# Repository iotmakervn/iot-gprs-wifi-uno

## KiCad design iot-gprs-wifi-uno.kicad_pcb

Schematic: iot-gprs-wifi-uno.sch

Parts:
C1: 10uF/50V; C_1210
C2: 10uF/50v; C_1210
C3: 1uF; C_0603
C4, C6, C15: 22pF; C_0603
C5, C10, C14, C22: 100nF; C_0603
C7, C8: 10uF/25V; C_1210
C9: 22uF; C_0603
C11: 100pF; C_0603
C12: 470uF; C_0603
C13: 10uF; C_0603
C16: 1uF/25V; C_1210
C17: 1uF/25V; C_0603
C18, C19, C20, C21: 0.1uF; C_0603
CON1: BARREL_JACK; dc_socket
D1, D3: SS24; do214aa
D2: D_Zener; SOD-80
D4: L_PWR; LED_0603
D5: LED_blue; LED_0603
L1: 22uH; Choke_SMD_Wuerth-WE-PD2-Typ-MS
P1: CAMERASOCKET; camera_socket24aaa
P2: SW2x6; SW_DIP_x6_W8.61mm_Slide_SMD_LowProfile
P3, P6: CONN_01X08; Pin_Header_Straight_1x08_Pitch2.54mm
P4: CONN_01X10; Pin_Header_Straight_1x10_Pitch2.54mm
P5: CONN_01X06; Pin_Header_Straight_1x06_Pitch2.54mm
R1, R3, R12, R16: NC; R_0603
R2, R15: 0K; R_0603
R4: 52.5K; R_0603
R5, R24, R25, R26, R27: 10K; R_0603
R6: 100R; R_0603
R7, R9, R28, R30: 470R; R_0603
R8: 10R; R_0603
R10, R11, R13: 10k; R_0603
R17: 3K/1%; R_0603
R18, R20, R21, R22, R23: 1K/1%; R_0603
R19: 470K; R_0603
R29: OR; R_0603
SMA1, SMA2: SMA; ANTEN_FP
SW1: SW_PUSH; SW_SPST_B3U-1000P
U1: usb_mini_b; USB_Micro-B
U2: MCP16311-MNY; MSOP-8_3x3mm_Pitch0.65mm
U3: CH340G; soic-16
U4: A20Module; a20module
U5: MCP6001R; SOT-23-5
U6: IRLM6402; SOT-23
U7: BD00GA5WEFJ; SOIJ-8_5.3x5.3mm_Pitch1.27mm
U8: SIM; SIM_HOLD_115A-ADA0-R02
X1: CRYSTAL_ABM3C; Crystal_SMD_3225_12MHz

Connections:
CAM_CLK: P1.13, U4.12
CAM_HREF: P1.9, U4.13
CAM_PCLK: P1.17, U4.11
CAM_PDN: P1.8, U4.41
CAM_RST: P1.6, U4.43
CAM_VSYNC: P1.7, U4.9
CAM_Y0: P1.19, U4.10
CAM_Y1: P1.21, U4.1
CAM_Y2: P1.22, U4.2
CAM_Y3: P1.20, U4.3
CAM_Y4: P1.18, U4.4
CAM_Y5: P1.16, U4.5
CAM_Y6: P1.14, U4.6
CAM_Y7: P1.12, U4.7
D+: U1.3 (D+), U3.5 (D+)
D-: U1.2 (D-), U3.6 (D-)
FLASH_EN: U4.38
FLASH_LED-: R22.2
GPIO3: U4.40
HST_RXD: P6.6, U4.37
HST_TXD: U4.36
I2C_SCL: R23.2, U4.31
I2C_SDA: R21.2, U4.30
unnamed: C3.1, U2.2 (Vcc)
unnamed: C4.1, X1.1
unnamed: C5.1, U2.7 (BOOST)
unnamed: C5.2, L1.1, U2.6 (SW)
unnamed: C10.1, U3.4 (3V)
unnamed: C22.1, R26.2
unnamed: CON1.1, D1.2 (A)
unnamed: D4.2 (A), R19.2
unnamed: D5.1 (K), R29.2
unnamed: D5.2 (A), R28.1
unnamed: P1.3, R21.1
unnamed: P1.5, R23.1
unnamed: P1.23, R20.1
unnamed: P1.24, R22.1
unnamed: R1.1, R2.2, U4.21
unnamed: R2.1, R3.2, SMA1.3
unnamed: R5.1, U4.18
unnamed: R7.1, U3.2 (TxD)
unnamed: R9.1, U3.3 (RxD)
unnamed: R10.2, R11.1, U5.3 (+)
unnamed: R12.2, R15.2, U4.39
unnamed: R4.2, R13.1, U2.1 (Vfb)
unnamed: R15.1, R16.2, SMA2.3
unnamed: R17.1, R18.1, U7.2 (FB)
unnamed: R29.1, R30.1, SW1.1
unnamed: U5.1, U6.1
SIM_CLK: U4.15, U8.3
SIM_DATA: U4.17, U8.7
SIM_RST: U4.14, U8.2
SLEEP: R5.2, U4.35
UART_RXD: P2.1, P2.2, R7.2, U4.33
UART_TXD: P2.3, P2.4, R9.2, U4.34
U_RXD: P2.12, P6.8
U_TXD: P2.10, P6.7
VCC3.3: C9.2, C11.2, C17.2, P3.5, R17.2, R19.1, R24.1, R25.1, R26.1, R28.2, U4.19, U5.4 (-), U7.1 (VO)
VCC3.9: C12.1, C13.1, D2.1 (K), R8.1, R20.2, U4.8, U4.45, U4.46
VCC5.0: C7.1, C8.1, C14.2, C15.1, C16.2, D3.1 (K), L1.2, P3.4, P3.7, R4.1, R8.2, U3.16 (VCC), U5.2 (V+), U6.3, U7.5 (EN), U7.8 (VCC)
VCC_USB: D3.2 (A), U1.1 (VBUS), U6.2
VDD_1V8: C20.2, P1.10, U4.32
VDD_2V8: C19.2, C21.2, P1.4, P1.11, U4.42
VSIM: C18.2, U4.16, U8.1, U8.6
Vin: C1.1, C2.1, D1.1 (K), P3.1, R10.1, U2.3 (EN), U2.4 (Vin)
WF_IO13: P2.6
WF_IO15: P2.5
WIFI_IO0: P4.10, R24.2, U4.28
WIFI_IO2: P4.9, R25.2, U4.27
WIFI_IO4: P4.1, P5.1, U4.29
WIFI_IO12: P4.6, P5.2, U4.24
WIFI_IO13: P2.7, P2.9, P3.6, P4.7, P6.4, U4.25
WIFI_IO15: P2.8, P2.11, P4.8, P5.3, P6.3, R6.2, R27.1, U4.26
WIFI_RST: P4.2, P6.5, R30.2, U4.20
WIFI_RXD: P4.5, U4.23
WIFI_TXD: P4.4, U4.22
XI: C6.1, U3.7 (XI), X1.3
XO: C1.2, C2.2, C3.2, C4.2, C6.2, C7.2, C8.2, C9.1, C10.2, C11.1, C12.2, C13.2, C14.1, C15.2, C18.1, C19.1, C20.1, C21.1, C22.2, CON1.2, CON1.3, D2.2 (A), P1.2, P1.15, P3.2, P3.3, P4.3, R1.2, R3.1, R6.1, R11.2, R12.1, R13.2, R16.1, R27.2, SMA1.1, SMA1.2, SMA2.1, SMA2.2, SW1.2, U1.5 (GND), U1.6 (GND), U2.5 (Pgnd), U2.8 (Agnd), U2.9 (PAD), U3.1 (GND), U3.8 (XO), U4.44, U5.5 (V-), U8.5, X1.2 (GND), X1.4 (GND)

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
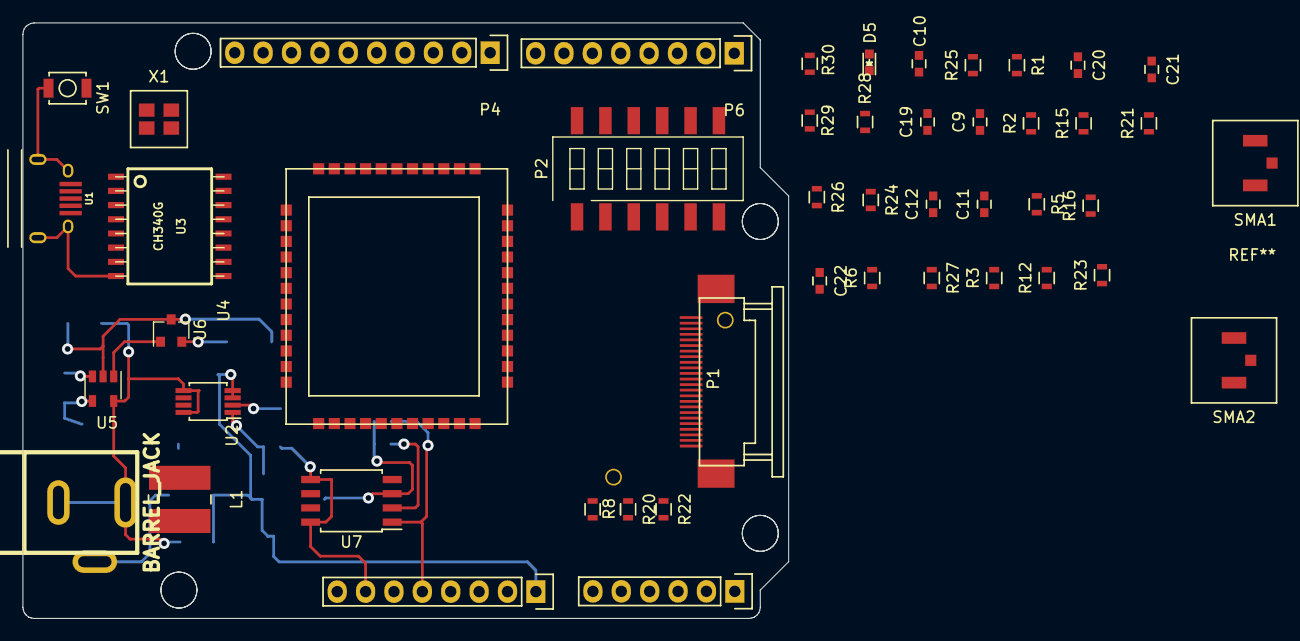
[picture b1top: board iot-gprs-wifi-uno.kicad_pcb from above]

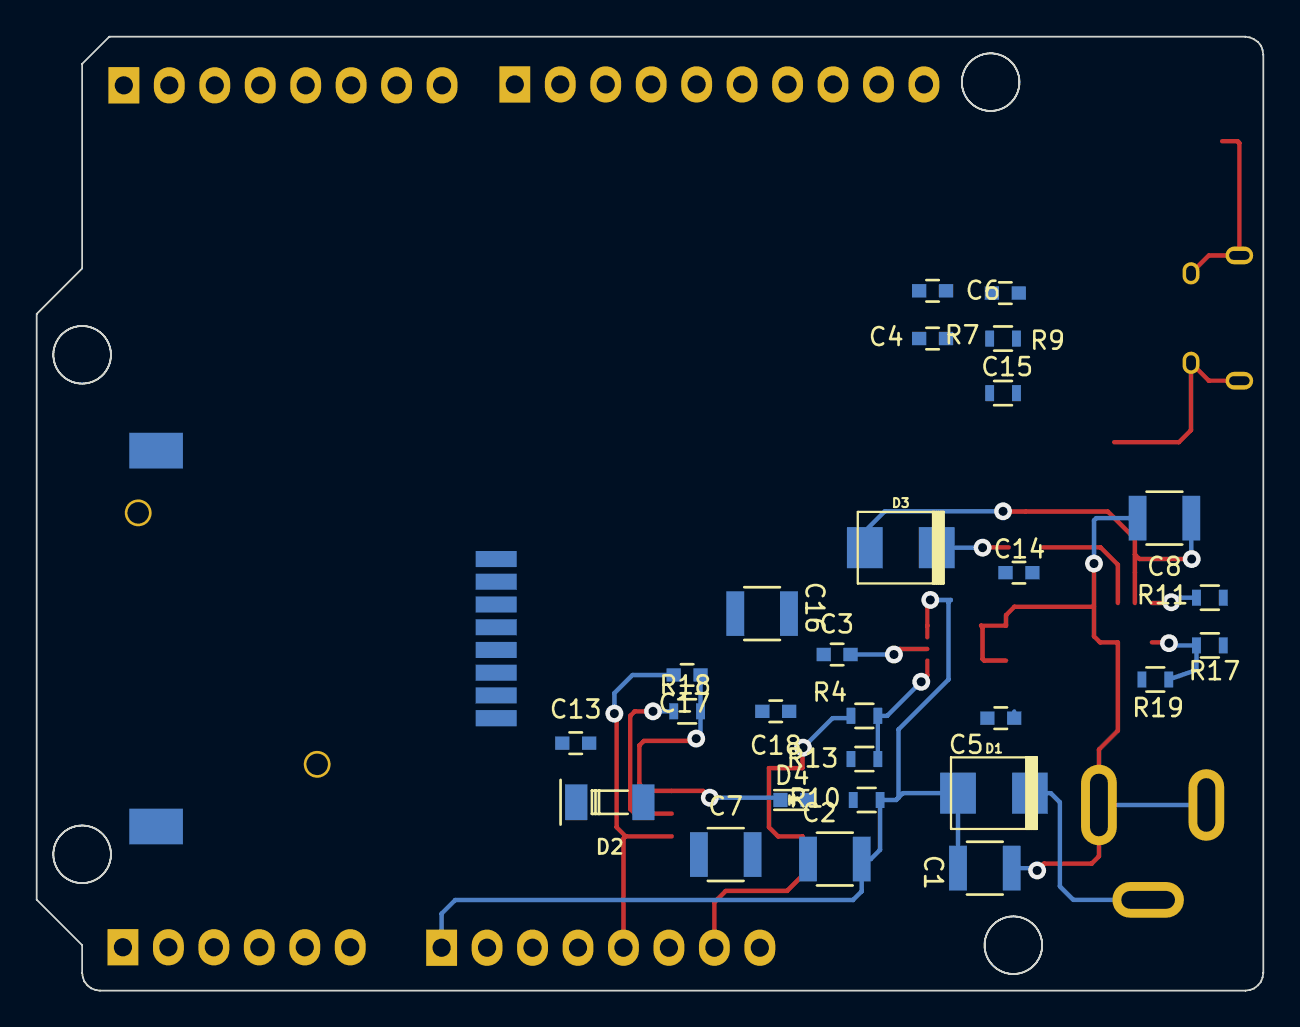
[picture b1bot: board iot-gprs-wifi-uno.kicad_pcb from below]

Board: 2 copper layers, 68.5 x 53.3 mm, 77 parts (29 on the bottom side), 73 nets.

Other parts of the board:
Arduino_Header: Val**; arduino_header

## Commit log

2016-12-22 add library of project;add kicad file of project
2016-12-31 add a20_module schematic add A20_module PCB add library add footprint library
2017-01-03 update Pcb,schematic error
2017-01-04 add .gitignore file add fp-lib-table
2017-01-07 update Kicad PCb iot-gprs-wifi-uno-hw
2017-01-09 update schematic iot-gprs-wifi-uno-hw add a20 pretty folder
